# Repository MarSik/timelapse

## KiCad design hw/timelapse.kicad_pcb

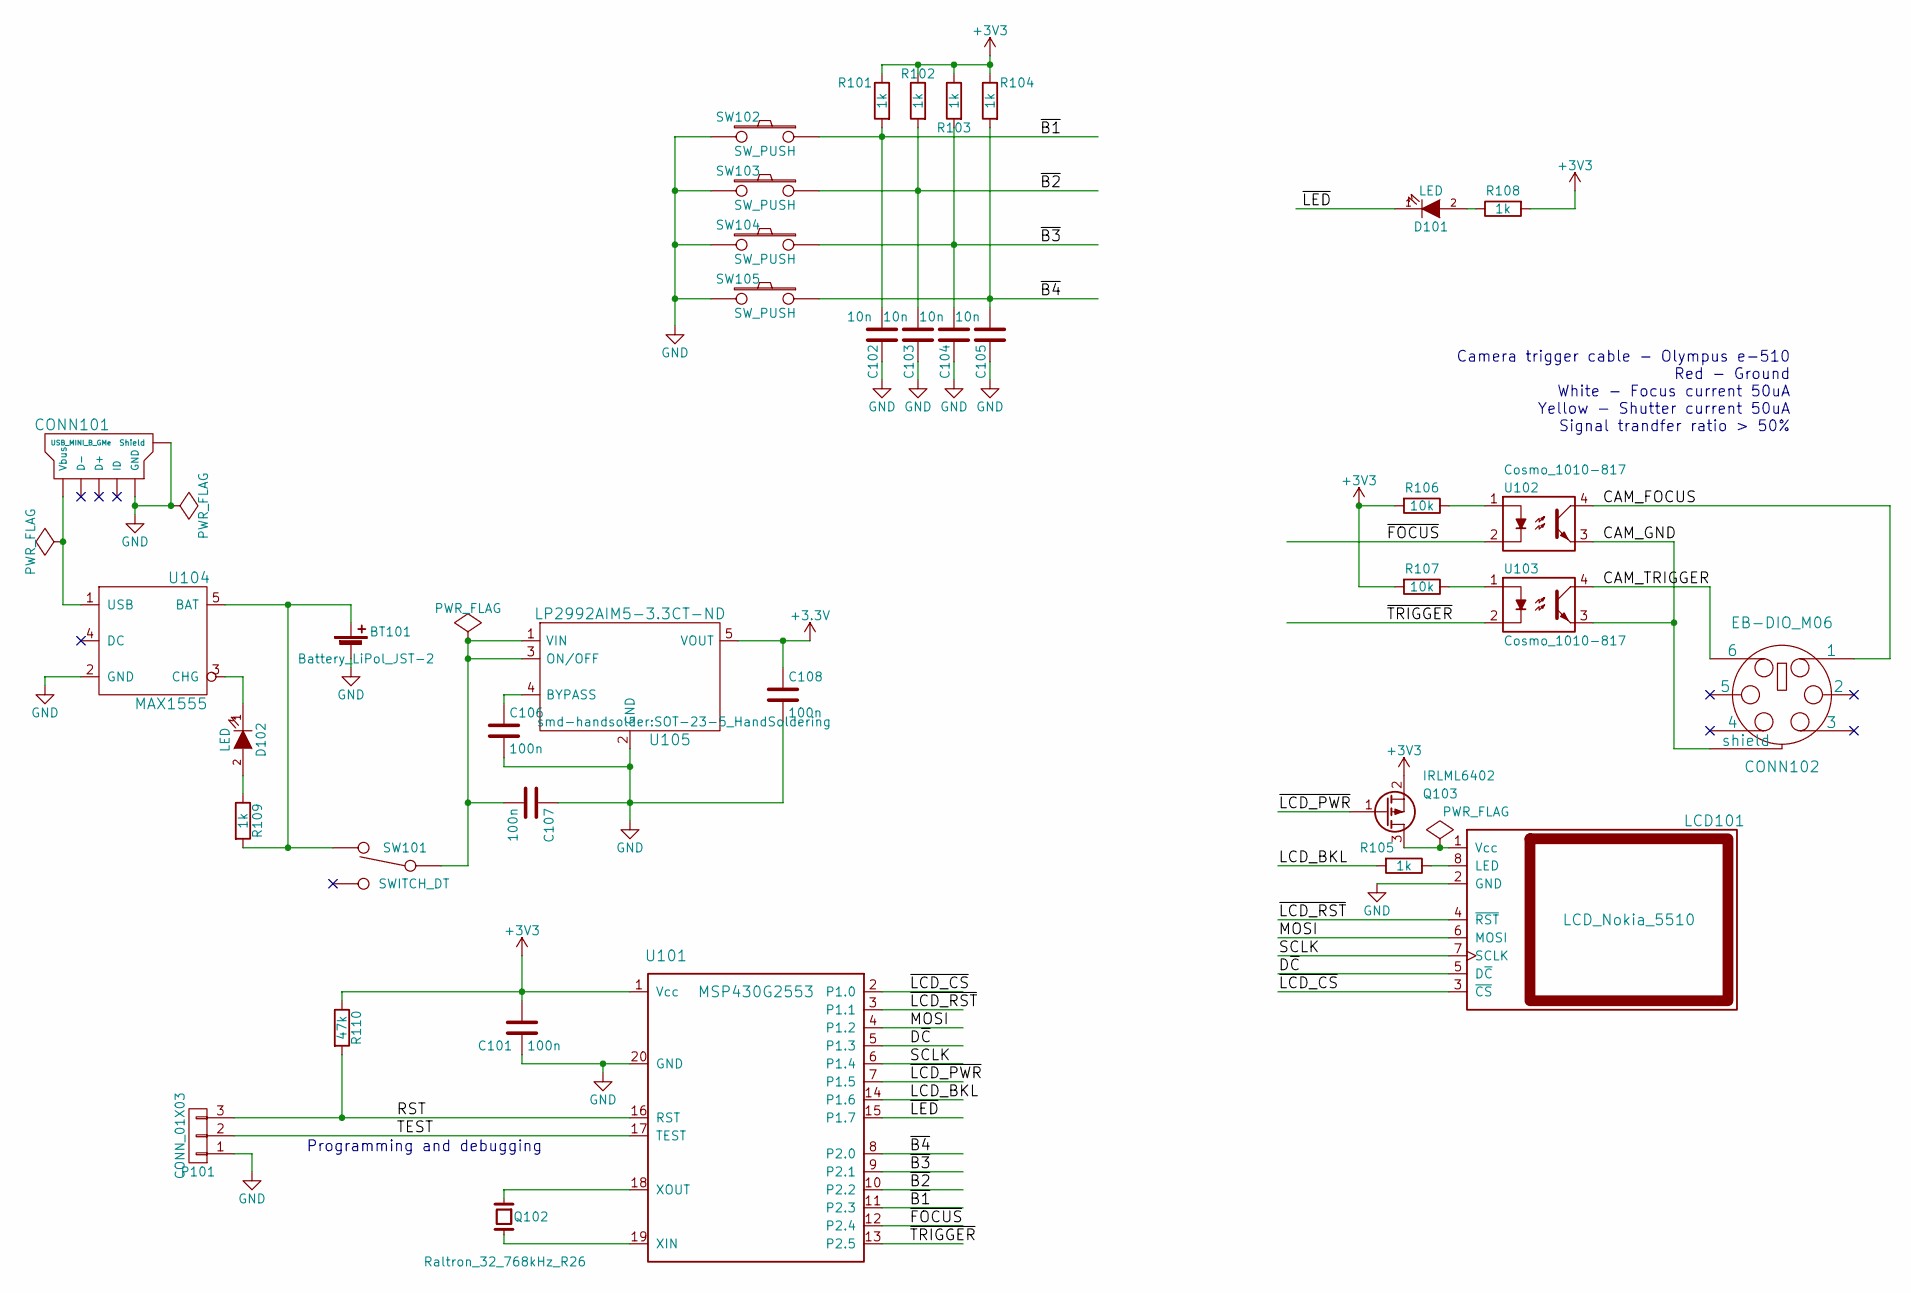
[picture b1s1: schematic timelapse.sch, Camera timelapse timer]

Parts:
BT101: Battery_LiPol_JST-2; Connector_JST-2_SMD_HandSoldering
C101, C106, C107, C108: 100n; C_1206_HandSoldering
C102, C103, C104, C105: 10n; C_1206_HandSoldering
CONN101: USB_MINI_B_GMe; Connector_USB-Mini-B_GMe_SMD
CONN102: EB-DIO_M06; Connector_DIN-6_EB-DIO-M06
D101, D102: LED; LED_L-1384_AL-1
LCD101: LCD_Nokia_5510
P101: CONN_01X03; Pin_Header_Angled_1x03
Q102: Raltron_32_768kHz_R26; Crystal_Round_Vertical_2mm
Q103: IRLML6402; SOT-23_HandSoldering
R101, R105, R108, R109: 1k; R_1206_HandSoldering
R102, R103, R104: 1k; Resistor_Horizontal_RM10mm
R106, R107: 10k; R_1206_HandSoldering
R110: 47k; R_1206
SW101: SWITCH_DT; Button_C&K_OS102011MA1QN1
SW102, SW103, SW104, SW105: SW_PUSH; Button_B3F-315X
U101: MSP430G2553; DIP-20_W300mil_LongPads
U102, U103: Cosmo_1010-817; DIP-4_W300mil_LongPads
U104: MAX1555; SOT-23-5_HandSoldering
U105: LP2992AIM5-3.3CT-ND; SOT-23-5_HandSoldering

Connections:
/CAM_FOCUS: CONN102.1, U102.4
/CAM_GND: CONN102.S (shield), U102.3, U103.3
/CAM_TRIGGER: CONN102.6, U103.4
/D~C: LCD101.5 (D~C), U101.5 (P1.3)
/MOSI: LCD101.6 (MOSI), U101.4 (P1.2)
/RST: P101.3, R110.2, U101.16 (RST)
/SCLK: LCD101.7 (SCLK), U101.6 (P1.4)
/TEST: P101.2, U101.17 (TEST)
/~B1: C102.1, R101.2, SW102.1, U101.11 (P2.3)
/~B2: C103.1, R102.2, SW103.1, U101.10 (P2.2)
/~B3: C104.1, R103.2, SW104.1, U101.9 (P2.1)
/~B4: C105.1, R104.2, SW105.1, U101.8 (P2.0)
/~FOCUS: U101.12 (P2.4), U102.2
/~LCD_BKL: R105.2, U101.14 (P1.6)
/~LCD_CS: LCD101.3 (~CS), U101.2 (P1.0)
/~LCD_PWR: Q103.1 (G), U101.7 (P1.5)
/~LCD_RST: LCD101.4 (~RST), U101.3 (P1.1)
/~LED: D101.1 (K), U101.15 (P1.7); also elsewhere on the board
/~TRIGGER: U101.13 (P2.5), U103.2
GND: BT101.2, C101.2, C102.2, C103.2, C104.2, C105.2, C106.2, C107.1, C108.2, CONN101.5 (GND), CONN101.S (Shield), LCD101.2 (GND), P101.1, SW102.2, SW103.2, SW104.2, SW105.2, U101.20 (GND), U104.2 (GND), U105.2 (GND)
unnamed: BT101.1, R109.2, SW101.1, U104.5 (BAT)
unnamed: C106.1, U105.4 (BYPASS)
unnamed: C107.2, SW101.2, U105.1 (VIN), U105.3 (ON/OFF)
unnamed: CONN101.1 (Vbus), U104.1 (USB)
unnamed: D101.2 (A), R108.1
unnamed: D102.1 (K), U104.3 (CHG)
unnamed: D102.2 (A), R109.1
unnamed: LCD101.1 (Vcc), Q103.3 (D)
unnamed: LCD101.8 (LED), R105.1
unnamed: Q102.1, U101.18 (XOUT)
unnamed: Q102.2, U101.19 (XIN)
unnamed: R106.1, U102.1
unnamed: R107.1, U103.1

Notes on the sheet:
Camera trigger cable - Olympus e-510 Red - Ground White - Focus current 50uA Yellow - Shutter current 50uA Signal trandfer ratio > 50%
Programming and debugging

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
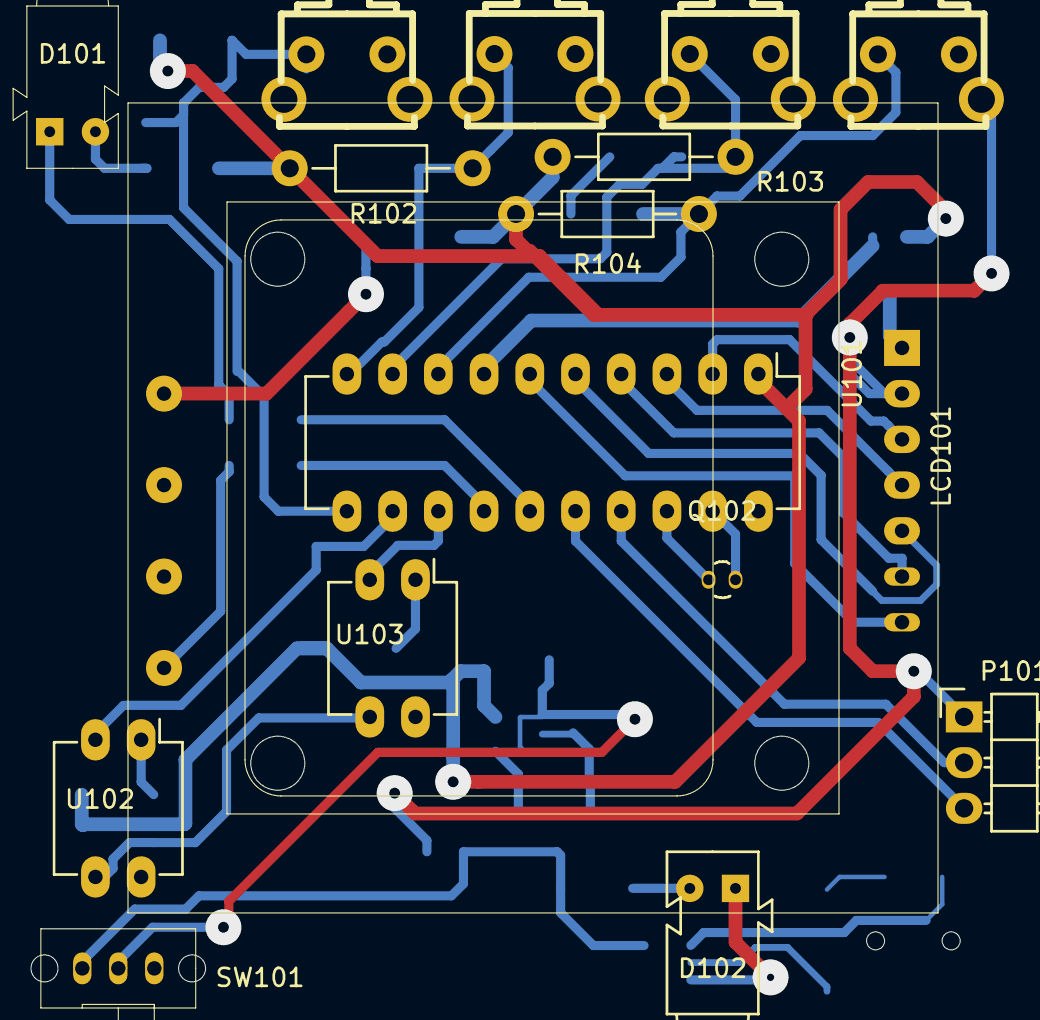
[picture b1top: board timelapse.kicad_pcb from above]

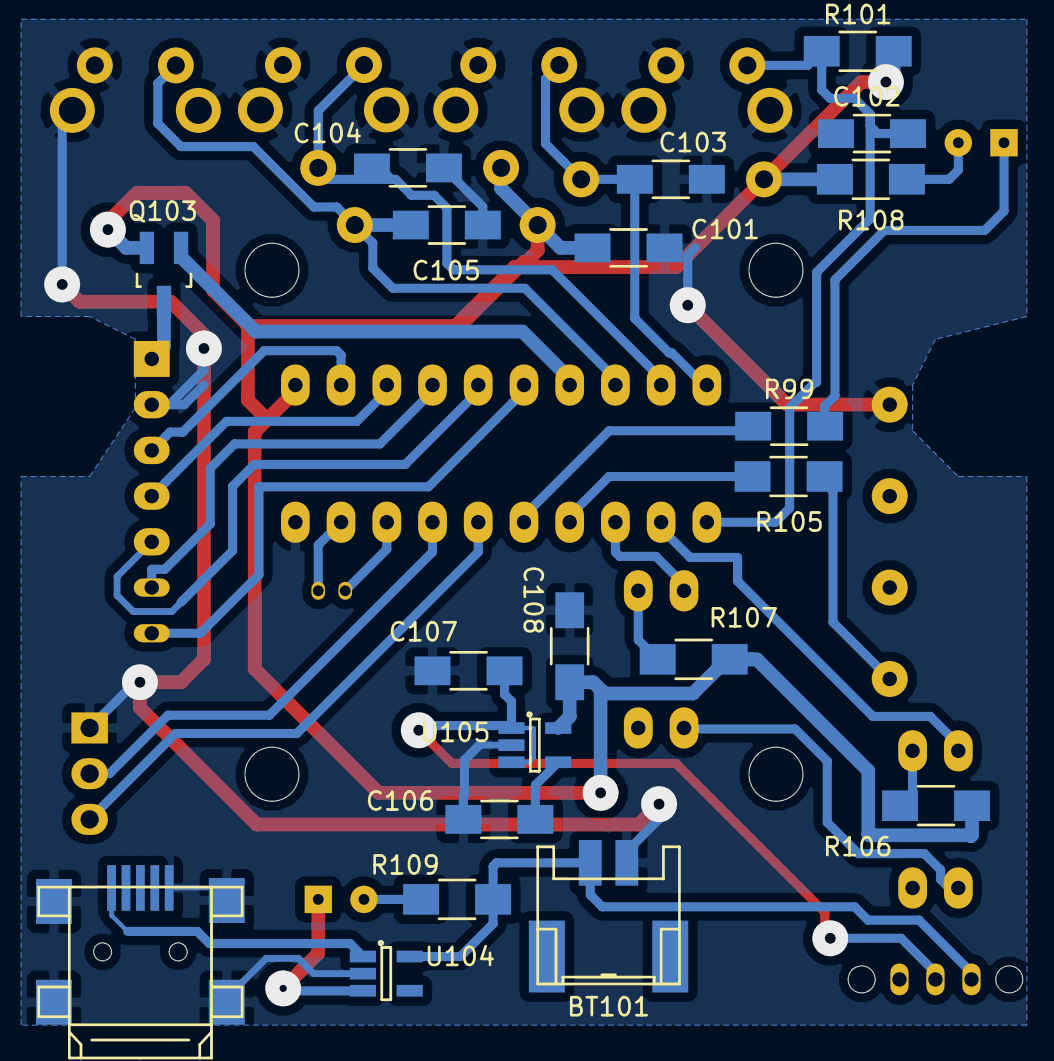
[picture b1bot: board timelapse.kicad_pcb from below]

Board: 2 copper layers, 36 parts (20 on the bottom side), 32 nets.

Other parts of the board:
R99: 0R; C_1206_HandSoldering

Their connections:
/~LED: R99.1, R99.2; also elsewhere on the board

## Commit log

2016-07-17 Timer UI and trigger timer logic
2016-07-17 Add battery measurement and display
2016-07-17 Add banner source image
2016-07-23 Flash the activity led only briefly to conserve power (TA0CCR2), all LCD timeouts are handled by TA0CCR1 now
2016-07-31 Add external trigger capability (remove LCD CS line)
2016-07-31 Some UI and trigger logic improvements
2016-07-31 AUX handling and style improvements
2017-12-20 Make this compatible with msp430-elf-gcc 6.x
